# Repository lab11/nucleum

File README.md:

Nucleum
====

Nucleum is a ½ inch² drop-in sensor node module designed to enable rapid
prototyping of Bluetooth Low Energy embedded devices. 
The core of Nucleum is the NRF51822
SoC with an Arm Cortex M0 and BLE radio stack. Nucleum also includes an
antenna, 4 kilo-bytes of non-volatile FRAM memory, an RTC, and a tri-color LED.

Nucleum is designed to have two different usage patterns. First, three sides
of the device have castellated headers allowing Nucleum to be directly
soldered onto a carrier PCB. Nucleum handles all of the computation and
communication while the carrier board supplies power and attaches
sensors or other peripherals. In the second option, Nucleum can function
as a complete sensor node. On the bottom are pads for a regulator
and a battery. If needed, a peripheral or sensor board can be stacked on
top using the headers as a bridge.

History
-------

Nucleum is directly derived from [Atum](http://www.github.com/lab11/atum). It
changes the radio protocol to BLE and adds an on-board programmer. Like Atum, 
it is intended to be a building block for sensor platforms that only includes
the features that a sensor board needs.
Visit the [Atum](http://www.github.com/lab11/atum) page to read more about its 
origins.

Name
----

Nucleum is the latin accusative form of 'Nucleus' which, like [Atum](http://www.github.com/lab11/atum),
represents a basic building block of matter. The 'LE' in the spelling of Nucleum 
indicates its use as a Bluetooth Low Energy prototyping board, and the 'UM' at
the end of Nucleum represents Nucleum's development at the University of Michigan.

Usage
-----

To use the NRF51822, you should run bare metal code that is built around
the Nordic SDK and software BLE stack (known as a softdevice). We provide
some examples and drivers for the chips on the Nucleum board. For more information
on getting started please see software/README.md.

PCB
---

Nucleum PCBs are panelized into 5x8 panels. They are designed to be 
1mm thick to allow for easy soldering of the castellations on the edge of
the board.

If you use the battery and regulator on the bottom of the board, you will have
to populate a 0 Ohm resistor to select regulated voltage. The selection is between 1.8V
and 3.0V. Position A is 1.8V and position B is 3.0V. The 1.8V selection was included
because it significantly lowers power draw on the NRF51822, but at this voltage
the RTC and FRAM may not work. Please see the
[hardware pdf](https://github.com/lab11/nucleum/raw/master/hardware/nucleum/rev_a/nucleum.pdf)
to locate this resistor selector.
DO NOT populate both position A and B; this will short the battery.

Pin Out
-------

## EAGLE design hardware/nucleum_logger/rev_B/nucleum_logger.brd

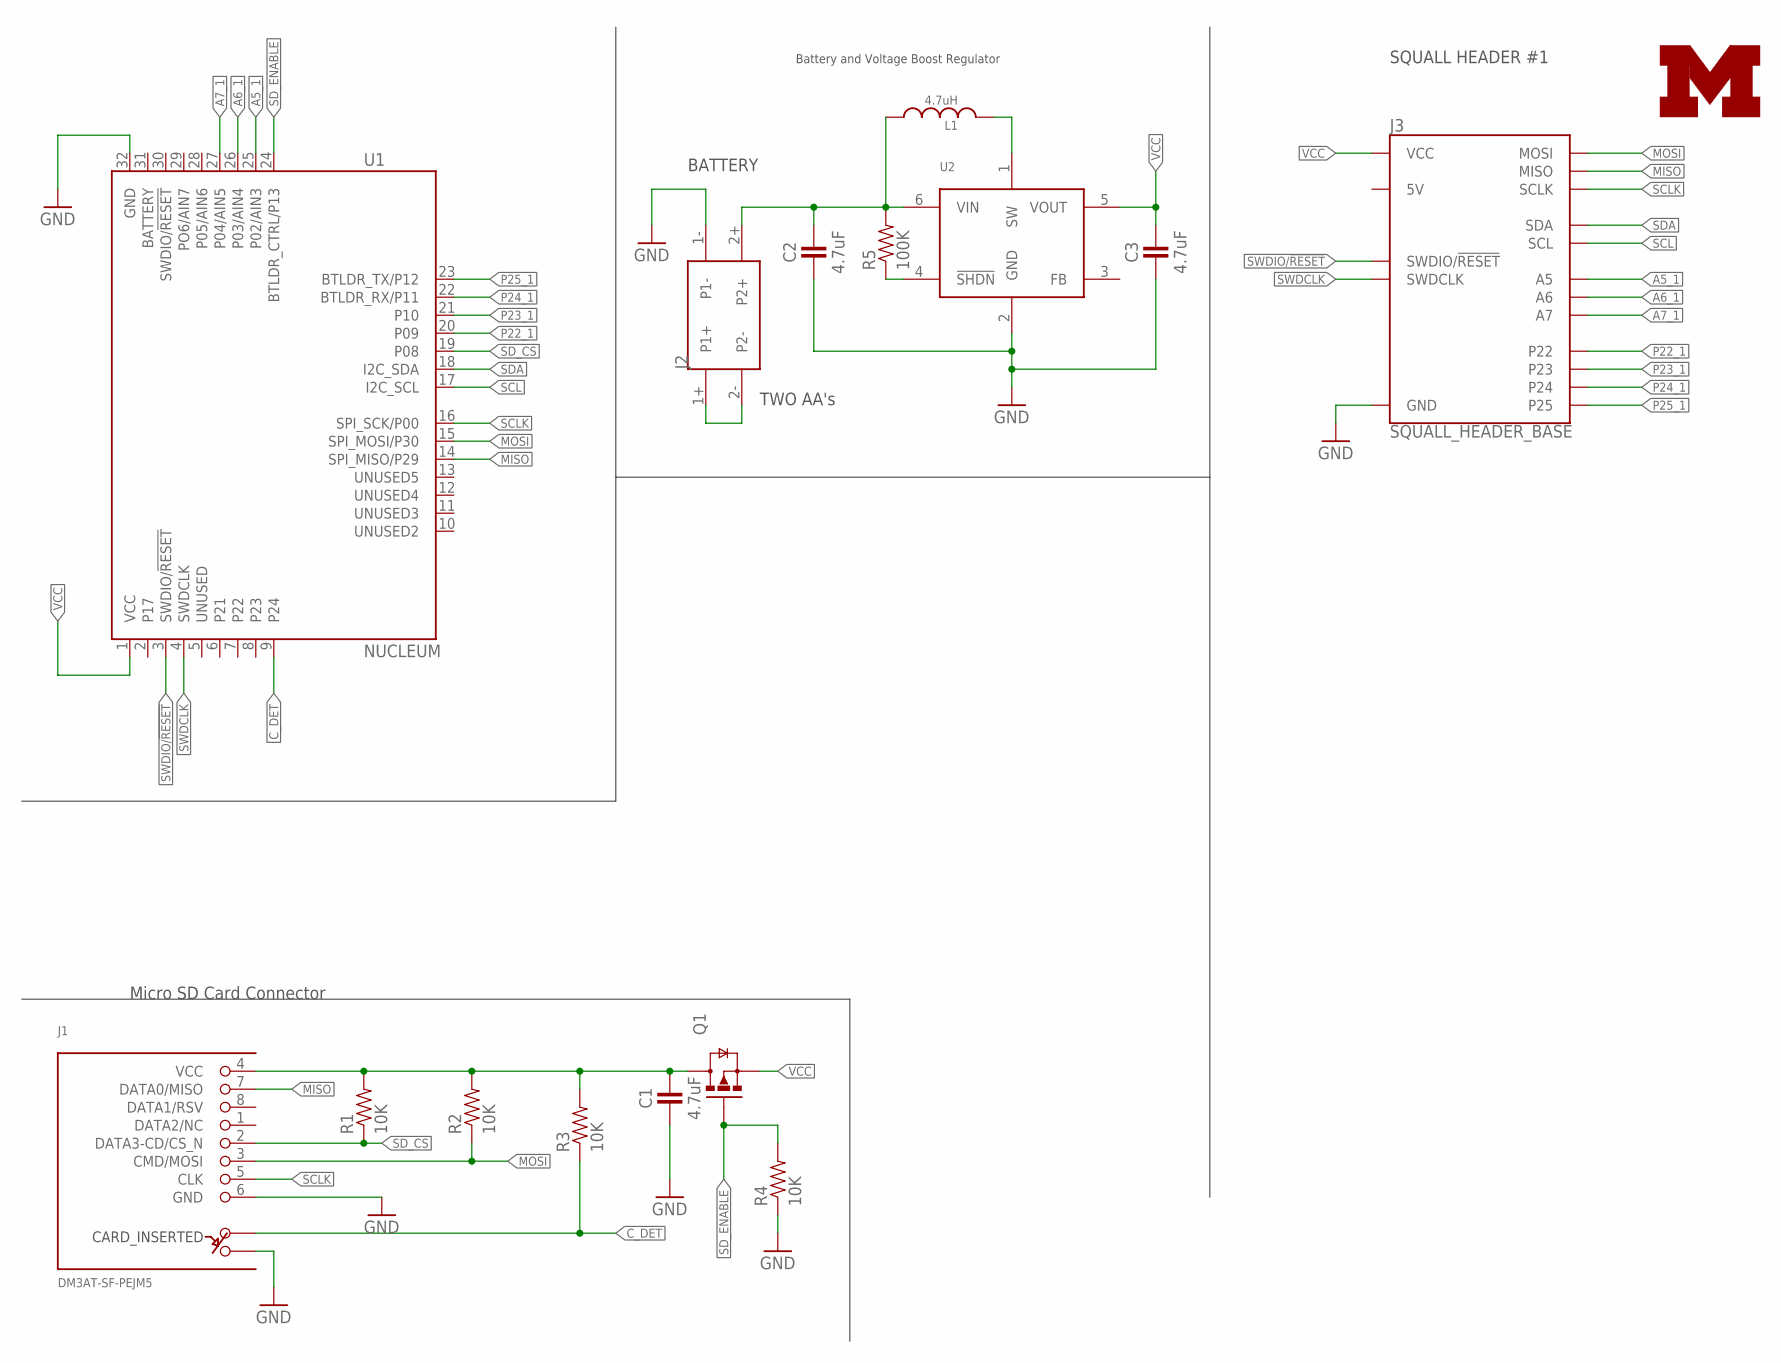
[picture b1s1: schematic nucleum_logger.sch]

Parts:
C1, C2, C3: 4.7uF; 0603_CAP
J1: DM3AT-SF-PEJM5
J2: AA_BAT_PACKSMD; AA_SMD
J3: SQUALL_HEADER_BASE; SQUALL_CARRIER
L1: 4.7uH; VLF3012A
LOGO1: UMICH_SOLID_SMALL; UMICH_SOLID_75MIL
Q1: NX3008PBK; SOT23-3
R1, R2, R3, R4: 10K; 0603-RES
R5: 100K; 0603-RES
U1: NUCLEUM
U2: AAT12173.3V; SOT-23-6

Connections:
A5_1: J3.B9 (A5), U1.25 (P02/AIN3)
A6_1: J3.B7 (A6), U1.26 (P03/AIN4)
A7_1: J3.B5 (A7), U1.27 (P04/AIN5)
C_DET: J1.A, R3.1, U1.9 (P24)
GND: C1.2, C2.2, C3.2, J1.6 (GND), J1.B, J2.1-, J3.A9 (GND), J3.A10 (GND), R4.1, U1.32 (GND), U2.2 (GND)
MISO: J1.7 (DATA0/MISO), J3.B8 (MISO), U1.14 (SPI_MISO/P29)
MOSI: J1.3 (CMD/MOSI), J3.B6 (MOSI), R2.1, U1.15 (SPI_MOSI/P30)
unnamed: J2.1+, J2.2-
unnamed: R5.1, U2.4 (!SHDN)
unnamed: L1.P$2 (2), U2.1 (SW)
P22_1: J3.A2 (P22), U1.20 (P09)
P23_1: J3.A4 (P23), U1.21 (P10)
P24_1: J3.A6 (P24), U1.22 (BTLDR_RX/P11)
P25_1: J3.A8 (P25), U1.23 (BTLDR_TX/P12)
SCL: J3.B3 (SCL), U1.17 (I2C_SCL)
SCLK: J1.5 (CLK), J3.B10 (SCLK), U1.16 (SPI_SCK/P00)
SDA: J3.B1 (SDA), U1.18 (I2C_SDA)
SD_CS: J1.2 (DATA3-CD/CS_N), R1.1, U1.19 (P08)
SD_ENABLE: Q1.1 (G), R4.2, U1.24 (BTLDR_CTRL/P13)
SWDCLK: J3.B2 (SWDCLK), U1.4 (SWDCLK)
SWDIO/!RESET: J3.B4 (SWDIO/!RESET), U1.3 (SWDIO/!RESET)
VCC: C3.1, J3.A1 (VCC), J3.A3 (VCC), Q1.2 (S), U1.1 (VCC), U2.5 (VOUT)
V_BAT: C2.1, J2.2+, L1.P$1 (1), R5.2, U2.6 (VIN)
V_SD: C1.1, J1.4 (VCC), Q1.3 (D), R1.2, R2.2, R3.2

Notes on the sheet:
Micro SD Card Connector
SQUALL HEADER #1
BATTERY
TWO AA's
Battery and Voltage Boost Regulator

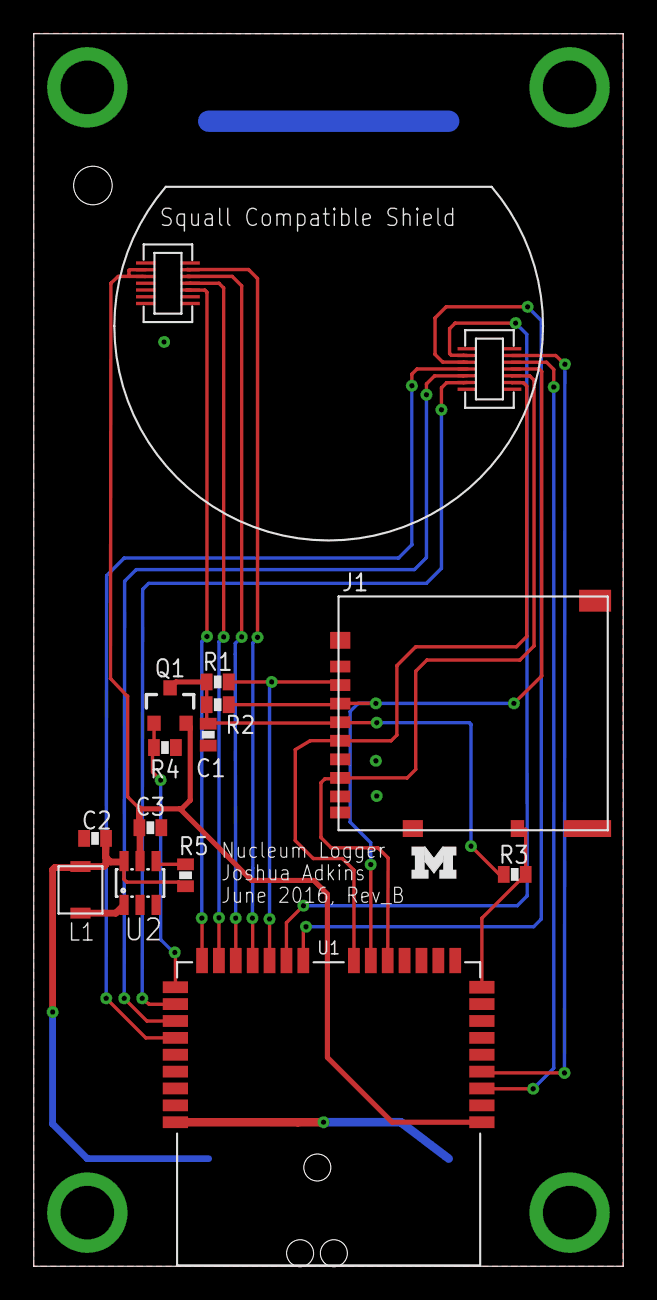
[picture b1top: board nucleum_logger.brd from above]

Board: 2 copper layers, 34.9 x 73.0 mm, 16 parts (1 on the bottom side), 24 nets.

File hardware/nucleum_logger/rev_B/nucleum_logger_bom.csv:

# Bill of Materials
# Converted from nucleum_logger_bom.xlsx
# Generated by bom_to_text.py

Part,Value,Device,Package,Description,DIGIKEY,MOUSER,NEWARK
C1,4.7uF,CAPACITOR0603_CAP,0603_CAP,0402 Capacitor,,,
C2,4.7uF,CAPACITOR0603_CAP,0603_CAP,0402 Capacitor,,,
C3,4.7uF,CAPACITOR0603_CAP,0603_CAP,0402 Capacitor,,,
J1,DM3AT-SF-PEJM5,DM3AT-SF-PEJM5,DM3AT-SF-PEJM5,CONN MICRO SD R/A PUSH-PUSH SMD,HR1964CT-ND,,
J2,AA_BAT_PACKSMD,AA_BAT_PACKSMD,AA_SMD,Types of AA Battery Packs,36-1012-ND,,
J3,SQUALL_HEADER_BASE,SQUALL_HEADER_BASE,SQUALL_CARRIER,Header for a sensor board on top of the Squall BLE tag board.,H11616CT-ND,,
L1,4.7uH,INDUCTORVLF3012A,VLF3012A,A very specific inductor,445-3225-1-ND,,
LOGO1,UMICH_SOLID_SMALL,UMICH_SOLID_SMALL,UMICH_SOLID_75MIL,,,,
Q1,NX3008PBK,NX3008PBK,SOT23-3,MOSFET - P Channel,568-10499-1-ND,"771-NX3008PBK,215",74T4665
R1,10K,RESISTOR,0603-RES,Resistor,,,
R2,10K,RESISTOR,0603-RES,Resistor,,,
R3,10K,RESISTOR,0603-RES,Resistor,,,
R4,10K,RESISTOR,0603-RES,Resistor,,,
R5,100K,RESISTOR,0603-RES,Resistor,,,
U1,NUCLEUM,NUCLEUM,NUCLEUM,Nucleum sensorboard prototyping module.,,,
U2,3.3V,AAT12173.3V,SOT-23-6,A Simple boost converter,863-1496-1-ND,,

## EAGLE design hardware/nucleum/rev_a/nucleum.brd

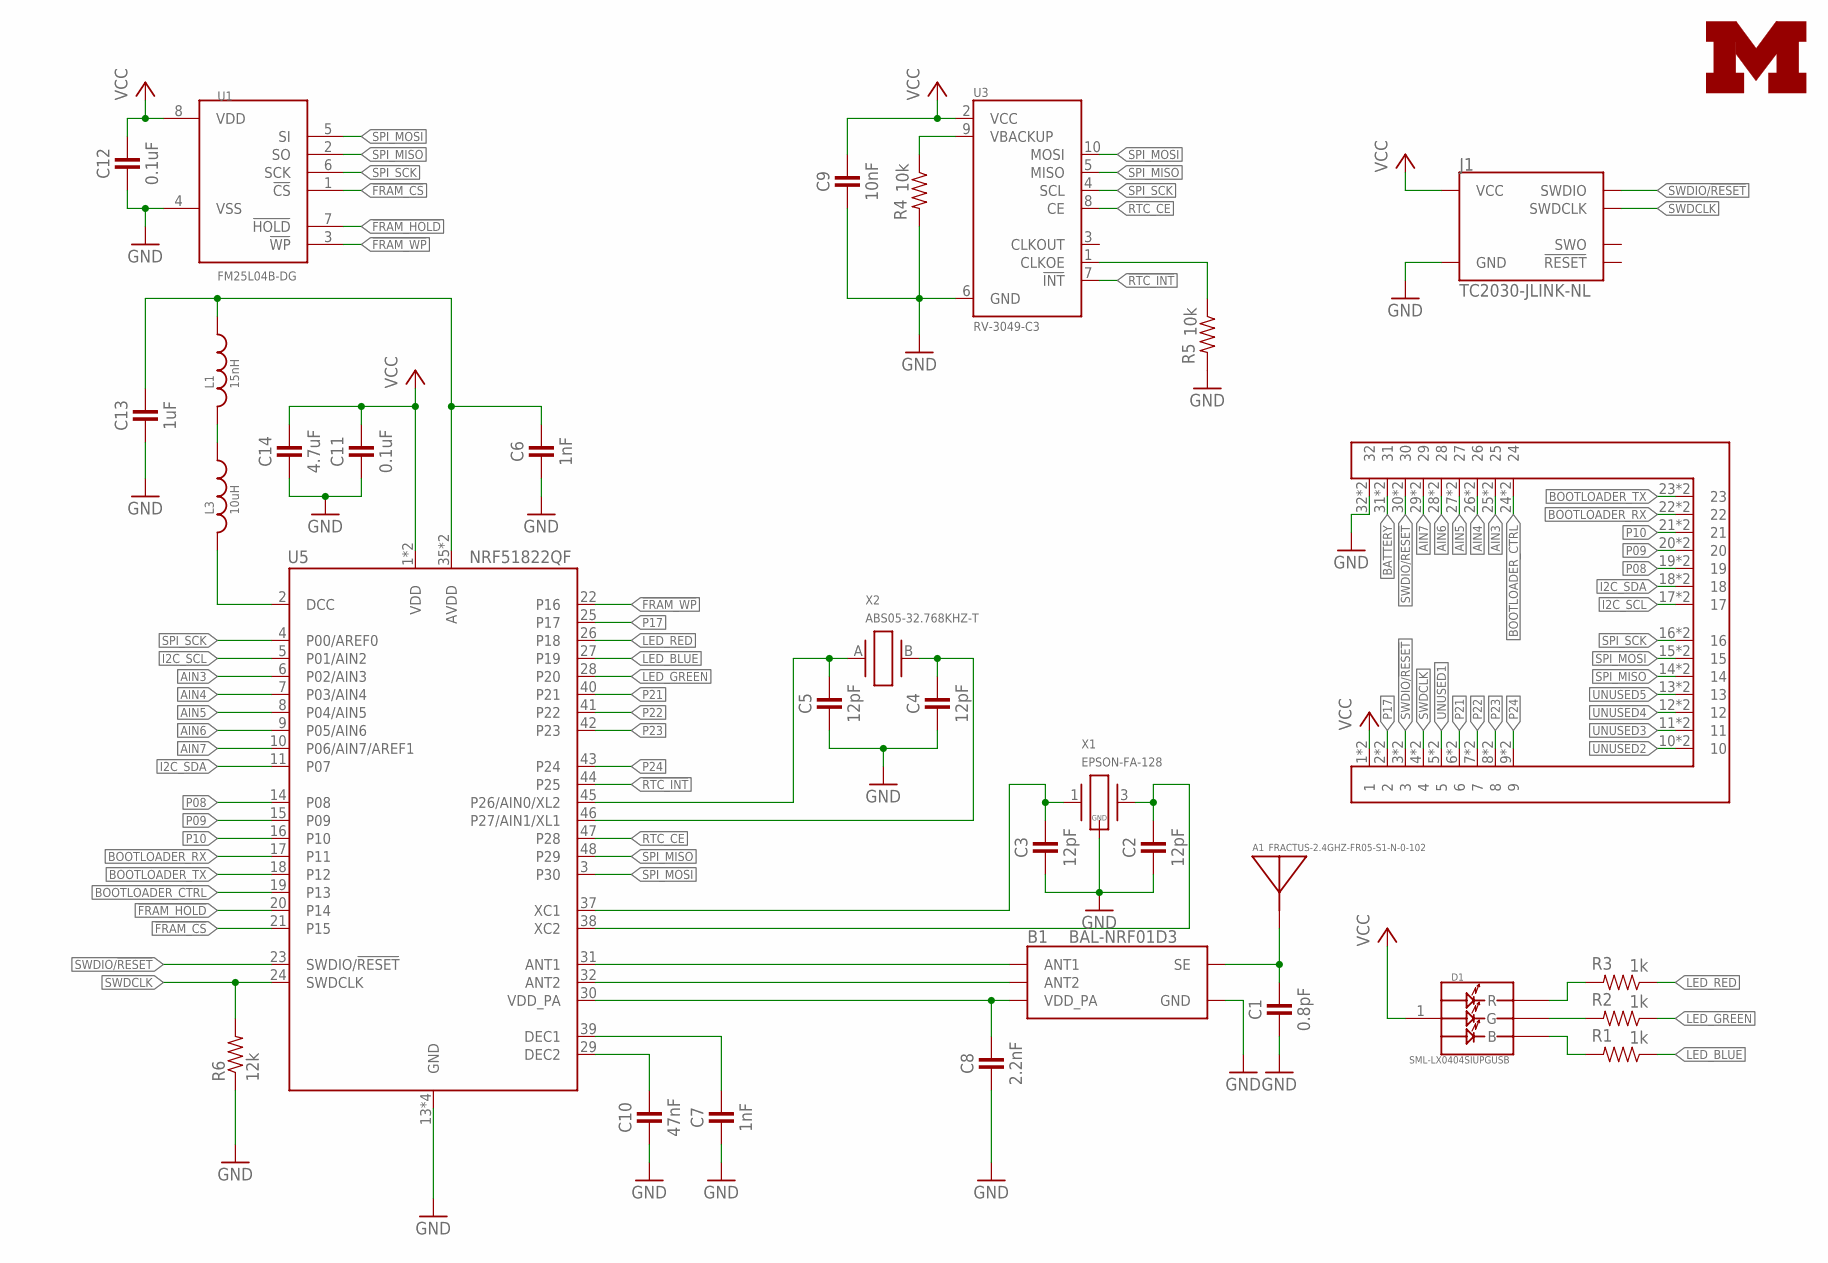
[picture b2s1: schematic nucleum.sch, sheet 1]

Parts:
A1: FRACTUS-2.4GHZ-FR05-S1-N-0-102; FRACTUS-ANTENNA-FR05-S1-N-0-102
B1: BAL-NRF01D3
C1: 0.8pF; 0402_CAP
C2, C3, C4, C5: 12pF; 0402_CAP
C6, C7: 1nF; 0402_CAP
C8: 2.2nF; 0402_CAP
C9: 10nF; 0402_CAP
C10: 47nF; 0402_CAP
C11, C12: 0.1uF; 0402_CAP
C13: 1uF; 0402_CAP
C14: 4.7uF; 0402_CAP
D1: SML-LX0404SIUPGUSB; 1MM_SQ_4PAD
J1: TC2030-JLINK-NL; TC2030-IDC-NL
J3: ATUM-HEADER
L1: 15nH; 0402_CAP
L3: 10uH; 0603_CAP
LOGO1: UMICH_SOLID_TINY; UMICH_SOLID_50MIL
R1, R2, R3: 1k; 0402_RES
R4, R5: 10k; 0402_RES
R6: 12k; 0402_RES
U1: FM25L04B-DG; TDFN-8
U3: RV-3049-C3; MICRO-CRYSTAL-C3
U5: NRF51822QF; QFN-48-6MM
X1: EPSON-FA-128; FA-128
X2: ABS05-32.768KHZ-T; ABS05

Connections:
!FRAM_CS: U1.1 (!CS), U5.21 (P15)
!FRAM_HOLD: U1.7 (!HOLD), U5.20 (P14)
!FRAM_WP: U1.3 (!WP), U5.22 (P16)
!RTC_INT: U3.7 (!INT), U5.44 (P25)
AIN3: J3.25, J3.25B (25), U5.6 (P02/AIN3)
AIN4: J3.26, J3.26B (26), U5.7 (P03/AIN4)
AIN5: J3.27, J3.27B (27), U5.8 (P04/AIN5)
AIN6: J3.28, J3.28B (28), U5.9 (P05/AIN6)
AIN7: J3.29, J3.29B (29), U5.10 (P06/AIN7/AREF1)
ANTENNA: A1.1, B1.SE, C1.1
BATTERY: J3.31, J3.31B (31); also elsewhere on the board
BOOTLOADER_CTRL: J3.24, J3.24B (24), U5.19 (P13)
BOOTLOADER_RX: J3.22, J3.22B (22), U5.17 (P11)
BOOTLOADER_TX: J3.23, J3.23B (23), U5.18 (P12)
GND: B1.GND, C1.2, C2.2, C3.2, C4.2, C5.2, C6.2, C7.2, C8.2, C9.2, C10.2, C11.2, C12.2, C13.2, C14.2, J1.5 (GND), J3.32, J3.32B (32), R4.2, R5.2, R6.1, U1.4 (VSS), U3.6 (GND), U5.13 (GND), U5.33 (GND), U5.34 (GND), U5.GND, X1.2 (GND), X1.4 (GND); also elsewhere on the board
I2C_SCL: J3.17, J3.17B (17), U5.5 (P01/AIN2)
I2C_SDA: J3.18, J3.18B (18), U5.11 (P07)
LED_BLUE: R1.1, U5.27 (P19)
LED_GREEN: R2.1, U5.28 (P20)
LED_RED: R3.1, U5.26 (P18)
unnamed: C5.1, U5.45 (P26/AIN0/XL2), X2.A (1)
unnamed: D1.2 (R), R3.2
unnamed: C3.1, U5.37 (XC1), X1.1
unnamed: C2.1, U5.38 (XC2), X1.3 (2)
unnamed: D1.4 (G), R2.2
unnamed: D1.3 (B), R1.2
unnamed: C4.1, U5.46 (P27/AIN1/XL1), X2.B (2)
unnamed: R4.1, U3.9 (VBACKUP)
unnamed: C10.1, U5.29 (DEC2)
unnamed: R5.1, U3.1 (CLKOE)
unnamed: C7.1, U5.39 (DEC1)
unnamed: B1.ANT1, U5.31 (ANT1)
unnamed: B1.ANT2, U5.32 (ANT2)
unnamed: B1.VCC (VDD_PA), C8.1, U5.30 (VDD_PA)
unnamed: C6.1, C13.1, L1.1, U5.35 (AVDD), U5.36 (AVDD)
unnamed: L1.2, L3.1
unnamed: L3.2, U5.2 (DCC)
P08: J3.19, J3.19B (19), U5.14 (P08)
P09: J3.20, J3.20B (20), U5.15 (P09)
P10: J3.21, J3.21B (21), U5.16 (P10)
P17: J3.2, J3.2B (2), U5.25 (P17)
P21: J3.6, J3.6B (6), U5.40 (P21)
P22: J3.7, J3.7B (7), U5.41 (P22)
P23: J3.8, J3.8B (8), U5.42 (P23)
P24: J3.9, J3.9B (9), U5.43 (P24)
RTC_CE: U3.8 (CE), U5.47 (P28)
SPI_MISO: J3.14, J3.14B (14), U1.2 (SO), U3.5 (MISO), U5.48 (P29)
SPI_MOSI: J3.15, J3.15B (15), U1.5 (SI), U3.10 (MOSI), U5.3 (P30)
SPI_SCK: J3.16, J3.16B (16), U1.6 (SCK), U3.4 (SCL), U5.4 (P00/AREF0)
SWDCLK: J1.4 (SWDCLK), J3.4, J3.4B (4), R6.2, U5.24 (SWDCLK)
SWDIO/!RESET: J1.2 (SWDIO), J3.3, J3.3B (3), J3.30, J3.30B (30), U5.23 (SWDIO/!RESET)
UNUSED1: J3.5, J3.5B (5)
UNUSED2: J3.10, J3.10B (10)
UNUSED3: J3.11, J3.11B (11)
UNUSED4: J3.12, J3.12B (12)
UNUSED5: J3.13, J3.13B (13)
VCC: C9.1, C11.1, C12.1, C14.1, D1.1 (VDD), J1.1 (VCC), J3.1, J3.1B (1), U1.8 (VDD), U3.2 (VCC), U5.1 (VDD), U5.12 (VDD); also elsewhere on the board

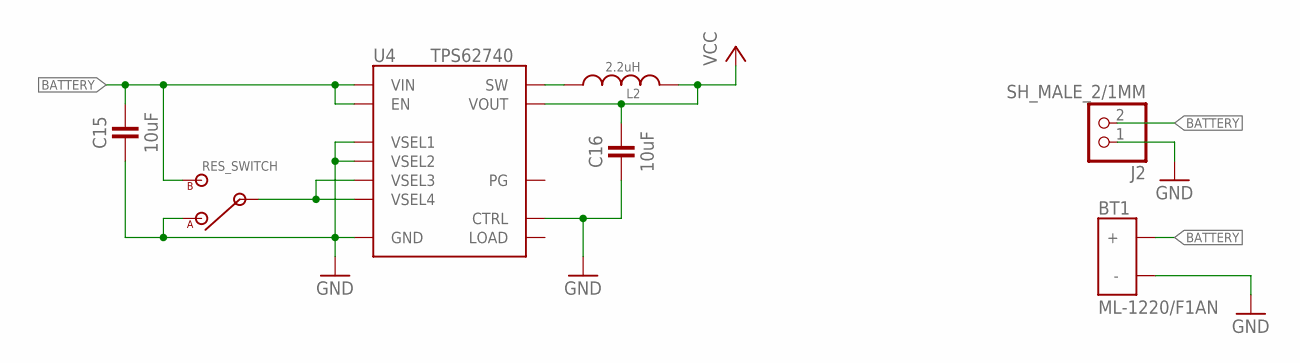
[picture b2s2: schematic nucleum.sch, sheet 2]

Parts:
BT1: ML-1220/F1AN; ML-1220/F1BN
C15, C16: 10uF; 0603_CAP; DIGIKEY 490-7316-1-ND
J2: SH_MALE_2/1MM; SH-1X2/1MM
L2: 2.2uH; MIPSZ201D
S1: RES_SWITCH
U4: TPS62740; R-PWSON-12

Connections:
BATTERY: BT1.POS (+), C15.1, J2.2, S1.B, U4.1 (VIN), U4.12 (EN); also elsewhere on the board
GND: BT1.NEG (-), C15.2, C16.2, J2.1, S1.A, U4.3 (GND), U4.4 (CTRL), U4.10 (VSEL2), U4.11 (VSEL1), U4.NC (GND); also elsewhere on the board
unnamed: L2.1, U4.2 (SW)
unnamed: S1.C (IN), U4.8 (VSEL4), U4.9 (VSEL3)
VCC: C16.1, L2.2, U4.5 (VOUT); also elsewhere on the board

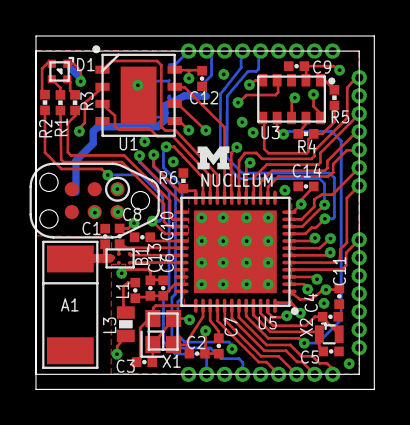
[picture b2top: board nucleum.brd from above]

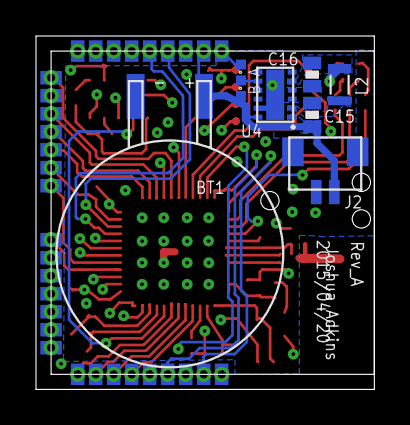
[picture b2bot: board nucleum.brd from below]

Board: 4 copper layers, 18.8 x 19.6 mm, 40 parts (7 on the bottom side), 59 nets.

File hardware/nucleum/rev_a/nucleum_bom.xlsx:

Part | Value | Device | Package | Description | DIGIKEY | MOUSER | NEWARK | RICHARDSON_RFPD
A1 | FRACTUS-2.4GHZ-FR05-S1-N-0-102 | FRACTUS-2.4GHZ-FR05-S1-N-0-102 | FRACTUS-ANTENNA-FR05-S1-N-0-102 | Fractus Compact Reach XtendTM chip antenna is engineered specifically for Bluet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 |  |  |  | FR05-S1-N-0102B
B1 | BAL-NRF01D3 | BAL-NRF01D3 | BAL-NRF01D3 | 50 ohm nominal input / conjugate match balun to nRF51422-QFAA, | 497-13637-1-ND | 511-BAL-NRF01D3
BT1 | ML-1220/F1AN | ML-1220/F1AN | ML-1220/F1BN | BATTERY LITH 3V RECHARGE PC PINS | P663-nd | 658-ML-1220/F1BN
C1 | 0.8pF | CAPACITOR | 0402_CAP | 0402 Capacitor
C2 | 12pF | CAPACITOR | 0402_CAP | 0402 Capacitor
C3 | 12pF | CAPACITOR | 0402_CAP | 0402 Capacitor
C4 | 12pF | CAPACITOR | 0402_CAP | 0402 Capacitor
C5 | 12pF | CAPACITOR | 0402_CAP | 0402 Capacitor
C6 | 1nF | CAPACITOR | 0402_CAP | 0402 Capacitor
C7 | 1nF | CAPACITOR | 0402_CAP | 0402 Capacitor
C8 | 2.2nF | CAPACITOR | 0402_CAP | 0402 Capacitor
C9 | 10nF | CAPACITOR | 0402_CAP | 0402 Capacitor
C10 | 47nF | CAPACITOR | 0402_CAP | 0402 Capacitor
C11 | 0.1uF | CAPACITOR | 0402_CAP | 0402 Capacitor
C12 | 0.1uF | CAPACITOR | 0402_CAP | 0402 Capacitor
C13 | 1uF | CAPACITOR | 0402_CAP | 0402 Capacitor
C14 | 4.7uF | CAPACITOR | 0402_CAP | 0402 Capacitor
C15 | 10uF | CAPACITOR0603_CAP | 0603_CAP | 0402 Capacitor | 490-7316-1-ND
C16 | 10uF | CAPACITOR0603_CAP | 0603_CAP | 0402 Capacitor | 490-7316-1-ND
D1 | SML-LX0404SIUPGUSB | SML-LX0404SIUPGUSB | 1MM_SQ_4PAD | 1mm^2 RGB LED | 67-2125-1-ND
J1 | TC2030-JLINK-NL | TC2030-JLINK-NL | TC2030-IDC-NL
J2 | SH_MALE_2/1MM | SH_MALE_2/1MM | SH-1X2/1MM | 1.0mm pitch/Disconnectable Crimp style connectors | 455-1788-2-ND
J3 | ATUM-HEADER | ATUM-HEADER | ATUM-HEADER | Castellated header for the Atum board.
L1 | 15nH | INDUCTOR0402 | 0402_CAP
L2 | 2.2uH | MIPSZ2012D | MIPSZ201D | FDK Multi-layer Power Inductor : MIPSZ2012D series (Very Small Type)
L3 | 10uH | INDUCTOR0603 | 0603_CAP
LOGO1 | UMICH_SOLID_TINY | UMICH_SOLID_TINY | UMICH_SOLID_50MIL
R1 | 1k | RESISTOR0402_RES | 0402_RES | Resistor
R2 | 1k | RESISTOR0402_RES | 0402_RES | Resistor
R3 | 1k | RESISTOR0402_RES | 0402_RES | Resistor
R4 | 10k | RESISTOR0402_RES | 0402_RES | Resistor
R5 | 10k | RESISTOR0402_RES | 0402_RES | Resistor
R6 | 12k | RESISTOR0402_RES | 0402_RES | Resistor
S1 | RES_SWITCH | RES_SWITCH | RES_SWITCH | 0402 Static Resistor Selector
U2 | FM25LBTDFN-8 | FM25LBTDFN-8 | TDFN-8 | IC FRAM 4KBIT 10MHZ 8SOIC | FM25L04B-DGRA-ND | 877-FM25L04B-DG
U3 | RV-3049-C3 | RV-3049-C3 | MICRO-CRYSTAL-C3 | The RV-3049-C3 is an ultra miniature Real-Time-Clock Module
U4 | TPS62740 | TPS62740 | R-PWSON-12 | 360nA Step Down Converter for Low Power Applications | 296-37134-1-ND | 595-TPS62740DSST | 27X9745
U5 | NRF51822QF | NRF51822QF | QFN-48-6MM | Multiprotocol Bluetooth® 4.0 low energy/2.4 GHz RF SoC | 1490-1032-1-ND | 949-NRF51822-QFAB-R7
X1 | EPSON-FA-128 | EPSON-FA-128 | FA-128 | MHz RANGE CRYSTAL UNIT
X2 | ABS05-32.768KHZ-T | ABS05-32.768KHZ-T | ABS05 | 32.768kHz Crystal | 535-11899-1-ND

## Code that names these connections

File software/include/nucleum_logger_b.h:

#ifndef NUCLEUM_H
#define NUCLEUM_H

#include <stdbool.h>

#include "nrf_gpio.h"

#ifndef DEVICE_NAME
#define DEVICE_NAME    "nucleum_logger"
#endif

#define LED_START      18
#define LED_0          18
#define LED_1          19
#define LED_2          20
#define LED_STOP       20


// This pin is mapped to the FTDI chip to all the device to enter the
// bootloader mode.
#define BOOTLOADER_CTRL_PIN  13
#define BOOTLOADER_CTRL_PULL NRF_GPIO_PIN_PULLUP

#define I2C_SCL_PIN   1
#define I2C_SDA_PIN   7

#define RX_PIN_NUMBER  11
#define TX_PIN_NUMBER  12
#define CTS_PIN_NUMBER 0
#define RTS_PIN_NUMBER 0
#define HWFC           false

#define SPI_SCK_PIN     0     /**< SPI clock GPIO pin number. */
#define SPI_MOSI_PIN    30     /**< SPI Master Out Slave In GPIO pin number. */
#define SPI_MISO_PIN    29     /**< SPI Master In Slave Out GPIO pin number. */
#define SPI_CS_PIN		8
#define SD_ENABLE_PIN	13		//power gates sd card
#define CD_PIN			24		//the card detect pin for the SD card
#define RV3049_CS		28
#define FRAM_HOLD		14
#define FRAM_CS			15
#define FRAM_WP			16

#define VOLTAGE_SENSE 	4
#define CURRENT_SENSE	3
#define SWITCH			9
#define SHDN		    10

bool platform_init ();


#endif

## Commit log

2015-03-27 copied original atum board to atum-le
2015-03-27 improved signal routing and mapping
2015-04-17 added README
2015-04-18 finished up schematic and did more routing
2015-04-18 added jtag, board routed but not DRCd
2015-04-19 fixed all drc errors
2015-04-19 added submodule of the nrf51 makefiles
2015-04-19 updated the lbr file to match le pin names
2015-04-19 changed lbr to allow for prog holes
2015-04-20 fixed programming breakout, moved silk
2015-04-20 moved a few vias
2015-04-21 finished routing cleanup and silk
2015-04-21 changed name to nucleum
2015-04-21 updated lbr file names
2015-04-21 finished layout and routing
2015-04-21 regain board annotation, finished/fix annotation erros
2015-04-21 renerated bom and renamed parts to ascending order
2015-04-21 sent files to sunstone
2015-04-23 added 3 led blink app
2015-04-23 removing bad submodule
2015-04-23 added submodule on master
2015-04-24 made makefile more generic
2015-04-24 added beacon app with generic Makefile
2015-04-25 changed software readme
2015-04-25 fixed README
2015-04-25 fixed readme again
2015-04-28 got the rv3049 driver compiling. still untested
2015-04-28 added time example that should advertise real time. untested
2015-04-28 added untested fram driver
2015-05-03 fixed examples so that they work with current hardware
2015-05-06 added pictures of nucleum
2015-05-06 updated readme, added gitignore
2015-05-06 added image and updated README
2015-06-02 added excel format BOM
2015-06-03 updated bom
2015-06-11 final bom update
2015-06-11 added panelized gerbers
2015-06-18 updated images and repackaged .zip for website
2015-06-23 added two new images
2015-06-23 added another image to README
2015-06-24 added panel comment to README
2015-11-09 update to nrf5x-base
2015-11-09 updated beacon
2015-11-11 no local submodule
2015-11-12 readme with advances in toolchain
2015-11-12 better header formatting
2015-11-24 add uart test app
2016-06-07 Will found a bug in the Nucleum library file where SWDIO and unused are switched
2016-06-08 working solar panel test program
2016-06-09 started a logger nucleum board that accepts squall shields
2016-06-09 fixed the i2c pin labels on the library part
2016-06-09 added working timer example for sdk 10
2016-06-09 main file currently running on the first signpost deployment
2016-06-09 did some final changes to the nucleum logger board
2016-06-09 fixed some attributes
2016-06-09 idk why these files are here, they aren't being used
2016-06-09 added the collection script for the test
2016-06-10 ran drc on the board
2016-06-10 fixed the solar panel test code to not break the NRF
2016-06-10 updated nrf5x-base in nucleum
2016-06-10 added a version of nucleum logger to be shipped
2016-06-12 added the capacitive touch app
2016-06-12 added the door schematic and the code for the PIR protection filtering
2016-06-12 changed the PIR sensor to an interrupt
2016-06-13 added the plotting and data from a test
2016-06-13 changed the time of the pulse
2016-06-13 changed some of the touch pir code to sense level and edges
2016-06-15 added the simple logger library - first tests worked
2016-06-15 added the new solar panel test
2016-06-15 added a gitignore finally
2016-06-15 setup spi every transfer - slow but reliable
2016-06-15 added the current sense driver and fixed a simple logger bug
2016-06-15 fixed the nucleum lbr part
2016-06-16 removed some of the data processing stuff out into another folder
2016-06-16 made a rev_A folder
2016-06-17 added rev_B of the nucleum logger board
2016-06-17 changed cvsense to not return negative values
2016-06-17 made a better sd card test
2016-06-17 fixed simple logger to allow for appending, smart header writing on new cards, and hot pluggability
2016-06-17 write extra byte after command per sd spec
    This effectively reduces power consumption from 15ma to 250ua between writes.
    the line of code was commented out with a warn ("may cause errors") message
    so this might need to be removed, but it worked on the Sandisk Ultra during
    my testing. Power savings are significant so it should be worth it.
2016-06-17 moving simple logger to nrf5x-base
2016-06-17 removed simple logger from nucleum to nrf5x-base
2016-06-17 updaed nrf5x-base for simple_logger
2016-06-17 added a rev_B of nucleum logger - we go to production
2016-06-17 Update FRAM to correct storage value
2016-06-23 added a new pin for logger
2016-06-23 added the newest nrf5xbase
2016-06-23 updated nrx5xbase
2016-06-23 new version of nrf5xbase
2016-06-23 updated voltage current logger
2016-06-23 updated the current/voltage sense board to update every reading
2016-06-23 reflect change in solar interface
2016-06-26 added the sd writing in thread context
2016-06-28 updated these apps for the chanfs simple logger library
2016-06-28 newest nrf5x-base
2016-06-29 tracking nrfxbase on master
2016-06-29 newer version of nrf5xbase
2016-07-01 added power_manage, saves a few ma
2016-07-06 got month working in the logger
2016-07-11 added code to diable current amplifier
2016-07-11 disabling spi when not using it
2016-07-12 fixed the disable cvsense code
2016-07-31 adding code for the replay board
2016-08-04 add nucleum test app for bgauge
2016-11-12 readme
2016-11-18 make readme pretty
2016-11-25 added code for voltage current logger b
    It does build
    It is completely untested. I could have messed up a pin
    Current or voltage equations could be wrong.
    Maybe nothing works at all
2016-11-29 Fixed #define typo in header
2016-12-02 fixed a bug in the SHDN timing
2017-01-07 updated software for cvsense boards
2017-01-07 updated cvsense_b config chip call
2017-01-09 fixed the resistance value of cvsenseb
2017-01-09 fixed the rtc makefile to remove all leading zeros
    This causes an octal problem during build occassionally
2017-05-15 fixed some wrong digikey numbers

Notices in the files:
parts and their libraries:
SparkFun-Aesthetics: Licensing: CC v3.0 Share-Alike You are welcome to use this library for commercial purposes.
